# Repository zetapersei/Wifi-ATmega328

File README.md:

# Wifi-ATmega328

A compact embedded board that combines an ESP8266 Wi-Fi module with an ATmega328P microcontroller for projects that need low-cost wireless connectivity and simple MCU control.

## Overview

This project provides a custom PCB designed for applications where an ATmega328P handles the logic and an ESP8266 provides Wi-Fi communication. The design is intended for embedded systems, IoT prototypes, sensor gateways, and small control boards that need a lightweight microcontroller plus wireless connectivity.

The board includes:

- ESP8266 Wi-Fi module
- ATmega328P microcontroller
- power regulation from a 12V / 5V input to the required logic voltages
- ICSP programming interface for the ATmega328P
- KiCad hardware design files for modification and reproduction

## Hardware architecture

The board is built around two processing elements:

- ATmega328P: used for application logic, sensor acquisition, timers, and control tasks
- ESP8266: used for Wi-Fi communication, network connectivity, and possible ESP-Now communication

The supplied power stage converts the board supply into the voltage levels required by the modules. A dedicated ICSP connector allows the ATmega328P to be programmed directly without removing it from the board.

The hardware project is available in the [hardware](./hardware) folder and includes the KiCad schematic and PCB files.

## Software options

The ESP8266 can be used with the AT command firmware, enabling communication with the ATmega328P through serial interfaces. In this setup, the MCU can delegate Wi-Fi tasks to the ESP8266 while continuing to handle local logic.

Recommended software paths:

- [WiFiEspAT library](https://github.com/jandrassy/WiFiEspAT.git) for AT firmware-based Wi-Fi communication
- [WiFiESPNow library](https://github.com/yoursunny/WifiEspNow) for ESP-Now communication scenarios

This makes the board suitable for both classic serial-controlled Wi-Fi use and low-latency peer-to-peer wireless communication.

## Repository structure

- `hardware/` — KiCad project files and PCB design assets
- `README.md` — project overview and documentation
- `LICENSE` — project license information

## Board views

### Top view

### Isometric view

## Typical use cases

- wireless sensor nodes
- smart actuator control boards
- IoT prototypes and test platforms
- embedded projects that need a classic AVR MCU plus Wi-Fi access

This board is especially useful when an AVR-based firmware stack is preferred while still requiring network connectivity through the ESP8266.

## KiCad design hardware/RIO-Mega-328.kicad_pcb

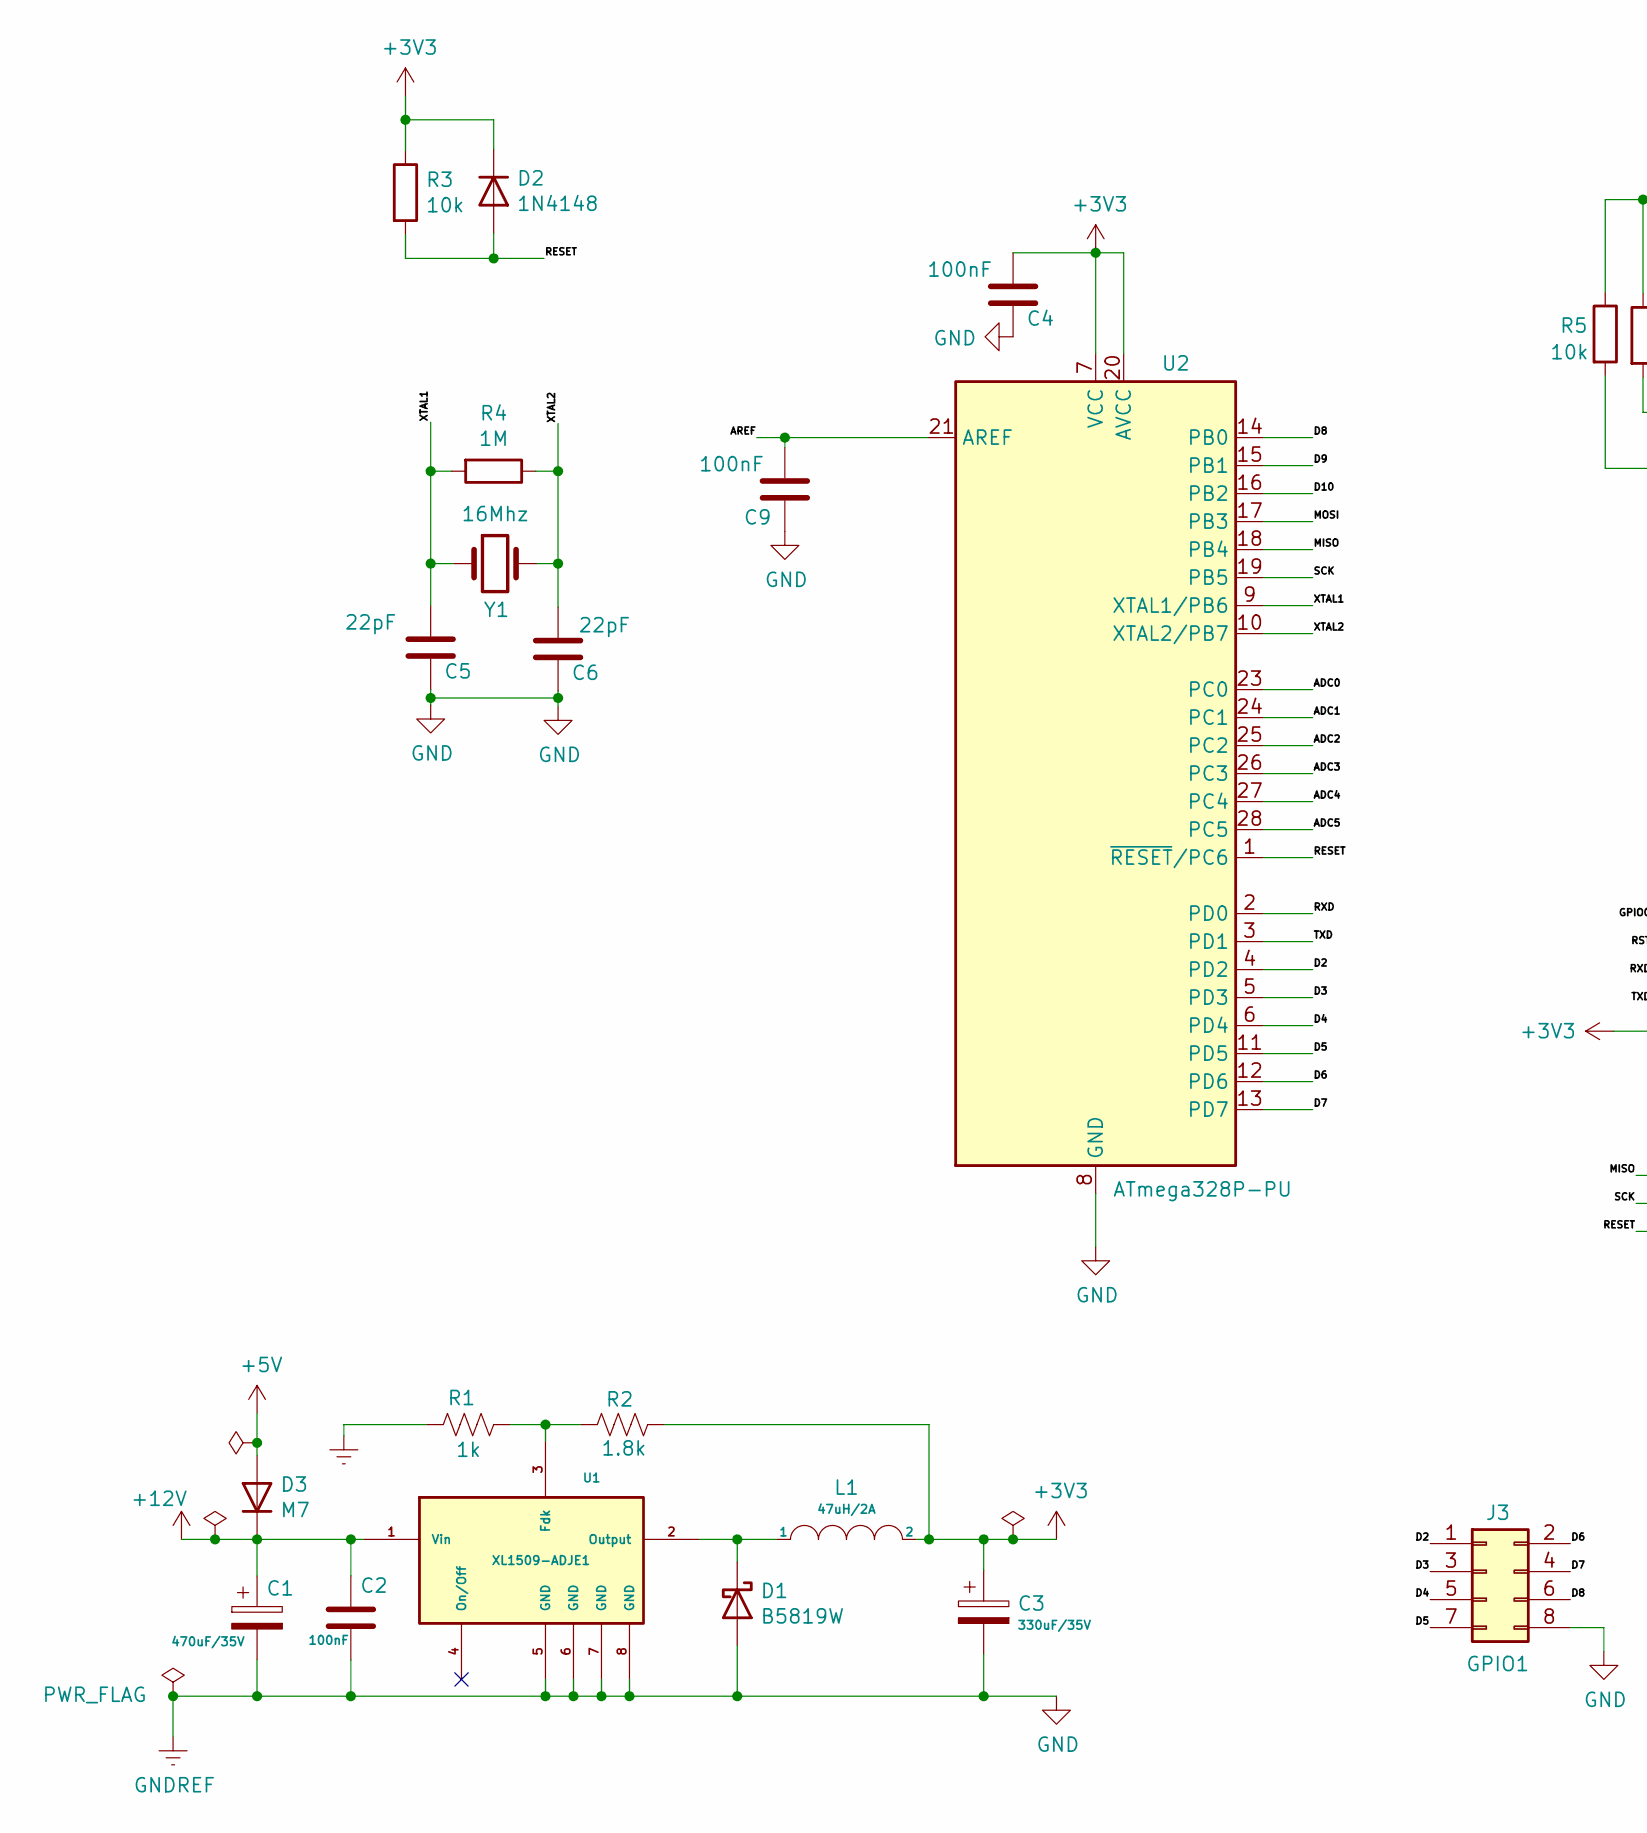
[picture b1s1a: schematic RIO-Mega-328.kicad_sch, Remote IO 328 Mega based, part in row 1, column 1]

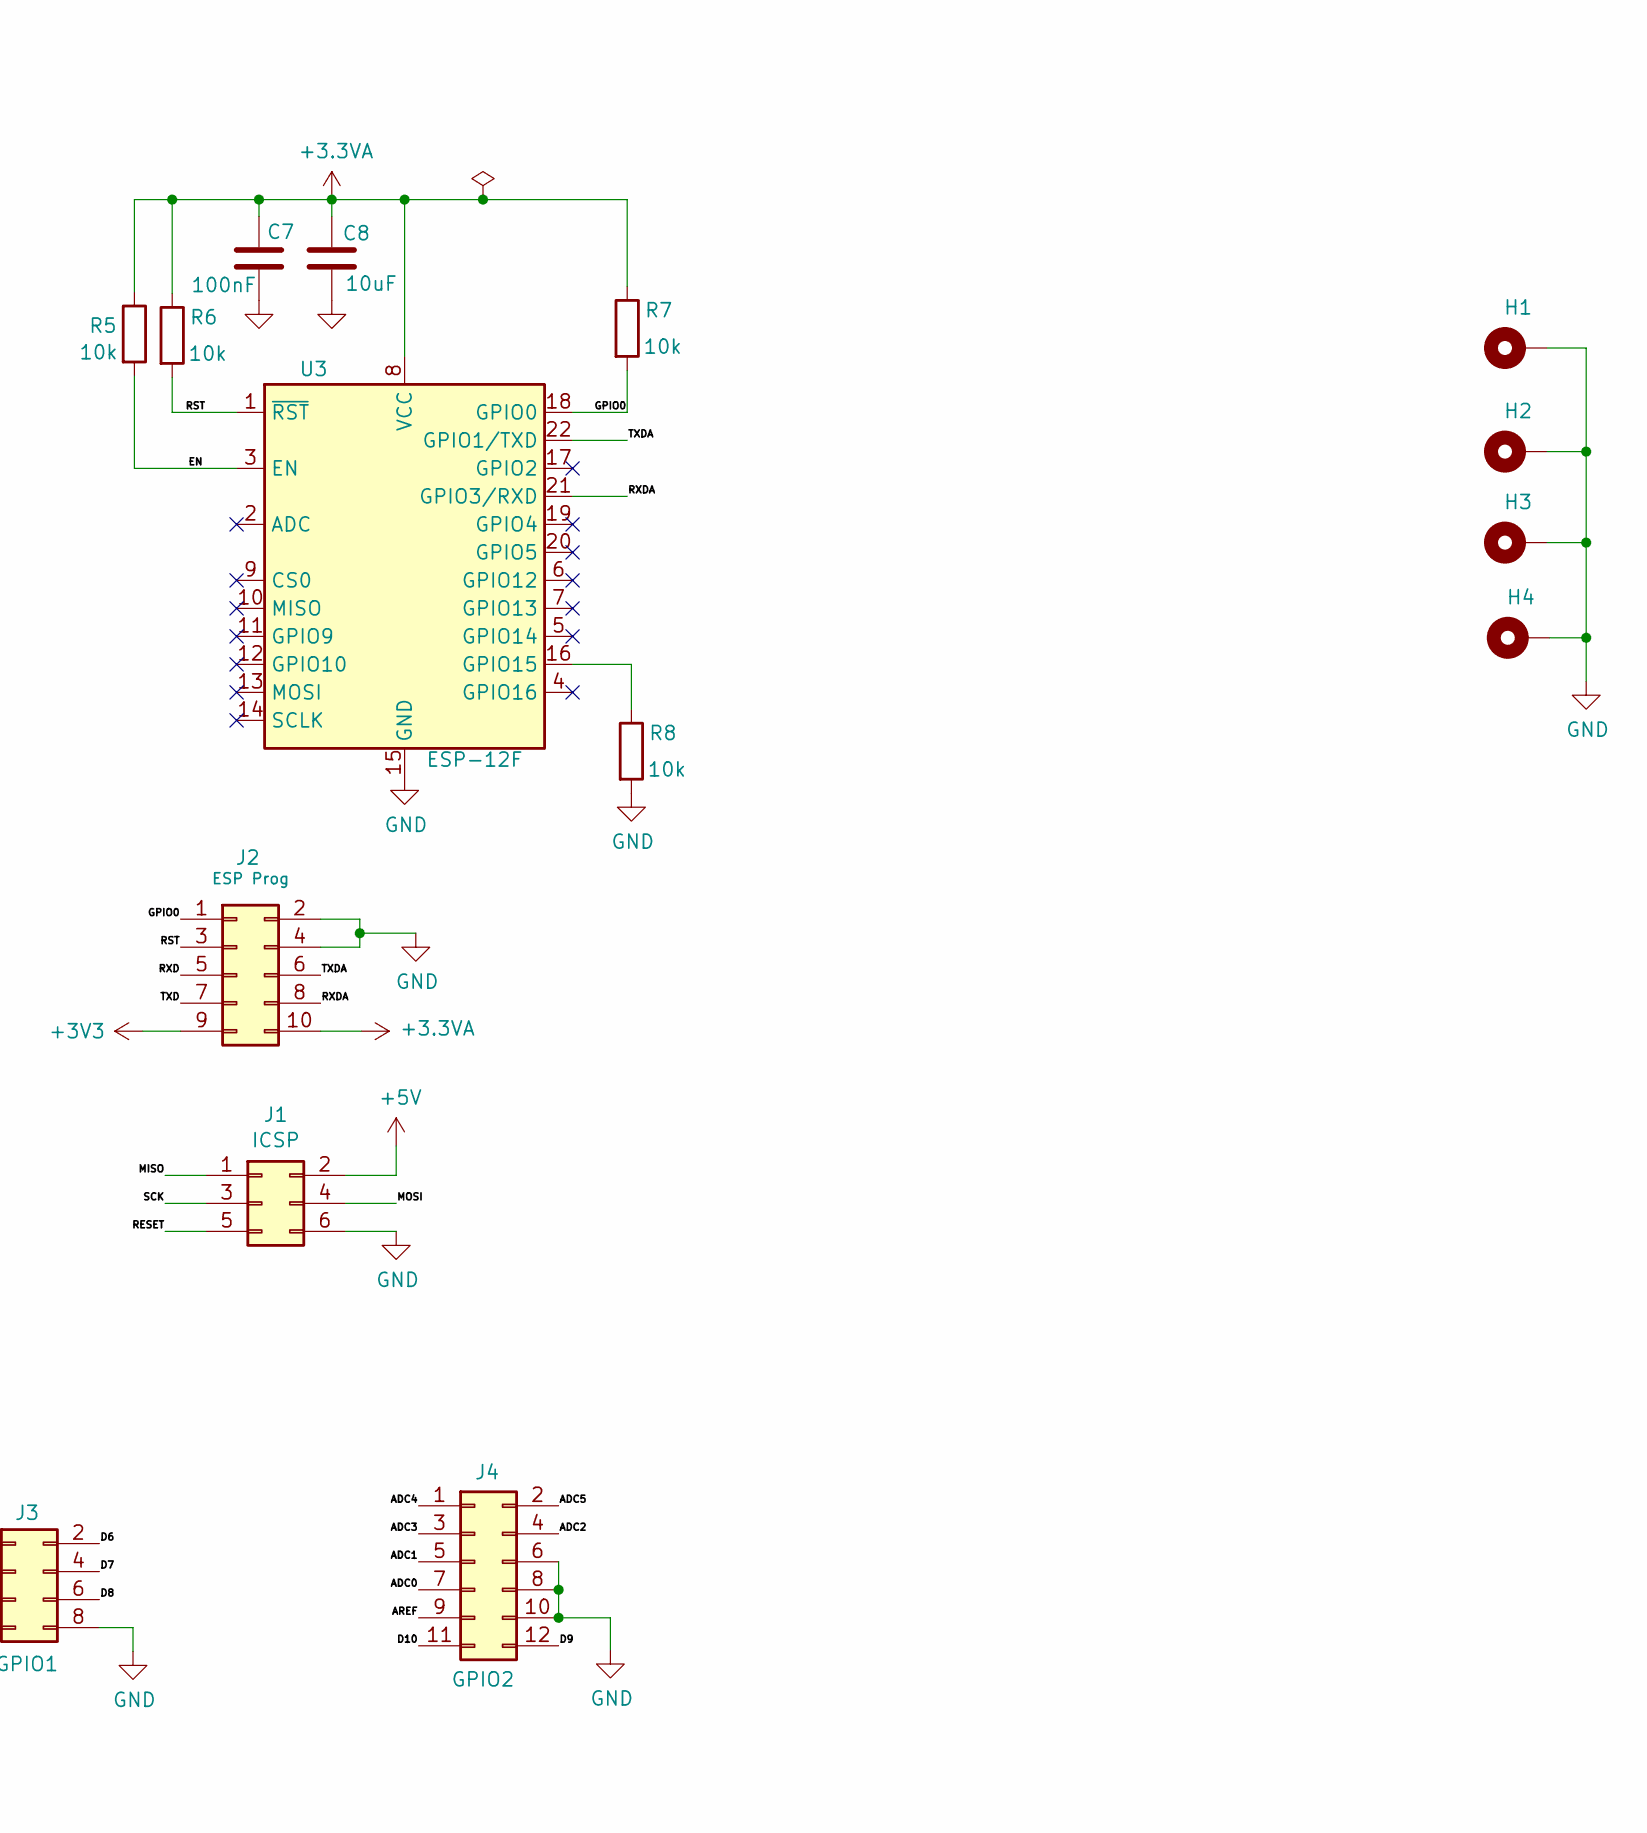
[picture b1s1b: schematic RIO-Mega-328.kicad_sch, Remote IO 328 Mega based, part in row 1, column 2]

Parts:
C1: 470uF/35V; CP_Radial_D8.0mm_P5.00mm
C2, C4, C7, C9: 100nF; C_0402_1005Metric; LCSC C1525
C3: 330uF/35V; CP_Radial_D8.0mm_P5.00mm
C5, C6: 22pF; C_0402_1005Metric; LCSC C1555
C8: 10uF; C_0603_1608Metric; LCSC C19702
D1: B5819W; D_SOD-123F; LCSC C8598
D2: 1N4148; D_SOD-123F; LCSC C81598
D3: M7; D_SOD-128; LCSC C95872
H1, H2, H3, H4: MountingHole_Pad; MountingHole_2.5mm_Pad_Via
J1: ICSP; PinHeader_2x03_P2.54mm_Vertical
J2: ESP Prog; PinHeader_2x05_P2.54mm_Vertical
J3: GPIO1; PinHeader_2x04_P2.54mm_Vertical
J4: GPIO2; PinHeader_2x06_P2.54mm_Vertical
L1: 47uH/2A; L_6.0x6.0x4.5-SWPA-Sunlord; LCSC C36414
R1: 1k; R_0402_1005Metric; LCSC C11702
R2: 1.8k; R_0402_1005Metric; LCSC C4177
R3: 10k; R_0402_1005Metric; LCSC C25774
R4: 1M; R_0603_1608Metric; LCSC C22935
R5, R6, R7, R8: 10k; R_0402_1005Metric; LCSC C25744
U1: XL1509-ADJE1; SOP-8_3.9x4.9mm_P1.27mm; LCSC C74192
U2: ATmega328P-PU; DIP-28_W7.62mm
U3: ESP-12F; ESP-12E; LCSC C82891
Y1: 16Mhz; Crystal_HC18-U_Vertical

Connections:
+3.3VA: C7.1, C8.1, J2.10, R5.1, R6.1, R7.1, U3.8 (VCC)
+3V3: C3.1, C4.1, D2.1 (K), J2.9, L1.2, R2.1, R3.1, U2.7 (VCC), U2.20 (AVCC)
+5V: D3.2 (A), J1.2
+12V: C1.1, C2.1, D3.1 (K), U1.1 (Vin)
/ADC0: J4.7, U2.23 (PC0)
/ADC1: J4.5, U2.24 (PC1)
/ADC2: J4.4, U2.25 (PC2)
/ADC3: J4.3, U2.26 (PC3)
/ADC4: J4.1, U2.27 (PC4)
/ADC5: J4.2, U2.28 (PC5)
/AREF: C9.1, J4.9, U2.21 (AREF)
/D2: J3.1, U2.4 (PD2)
/D3: J3.3, U2.5 (PD3)
/D4: J3.5, U2.6 (PD4)
/D5: J3.7, U2.11 (PD5)
/D6: J3.2, U2.12 (PD6)
/D7: J3.4, U2.13 (PD7)
/D8: J3.6, U2.14 (PB0)
/D9: J4.12, U2.15 (PB1)
/D10: J4.11, U2.16 (PB2)
/EN: R5.2, U3.3 (EN)
/GPIO0: J2.1, R7.2, U3.18 (GPIO0)
/MISO: J1.1, U2.18 (PB4)
/MOSI: J1.4, U2.17 (PB3)
/RESET: D2.2 (A), J1.5, R3.2, U2.1 (~RESET/PC6)
/RST: J2.3, R6.2, U3.1 (~RST)
/RXD: J2.5, U2.2 (PD0)
/RXDA: J2.8, U3.21 (GPIO3/RXD)
/SCK: J1.3, U2.19 (PB5)
/TXD: J2.7, U2.3 (PD1)
/TXDA: J2.6, U3.22 (GPIO1/TXD)
/XTAL1: C5.1, R4.2, U2.9 (XTAL1/PB6), Y1.1
/XTAL2: C6.1, R4.1, U2.10 (XTAL2/PB7), Y1.2
GND: C1.2, C2.2, C3.2, C4.2, C5.2, C6.2, C7.2, C8.2, C9.2, D1.2 (A), H1.1, H2.1, H3.1, H4.1, J1.6, J2.2, J2.4, J3.8, J4.6, J4.8, J4.10, R1.2, R8.2, U1.5 (GND), U1.6 (GND), U1.7 (GND), U1.8 (GND), U2.8 (GND), U2.22 (GND), U3.15 (GND)
unnamed: D1.1 (K), L1.1, U1.2 (Output)
unnamed: R1.1, R2.2, U1.3 (Fdk)
unnamed: R8.1, U3.16 (GPIO15)

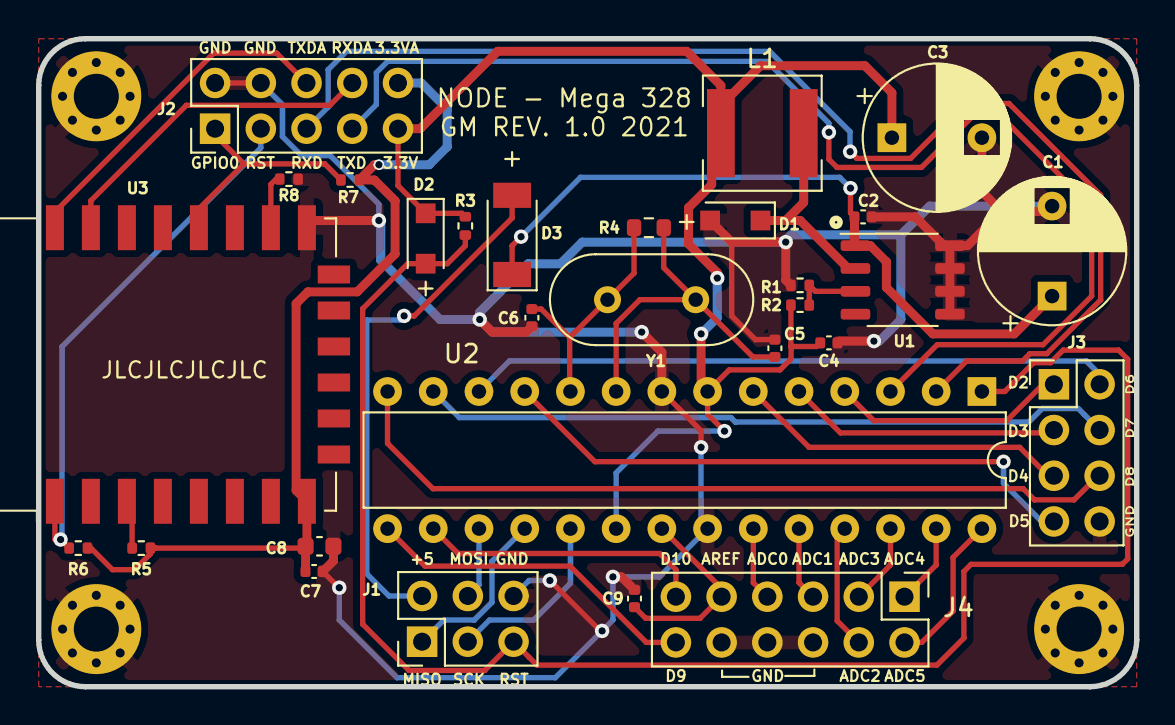
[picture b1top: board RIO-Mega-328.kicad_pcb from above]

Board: 2 copper layers, 61.0 x 36.0 mm, 33 parts (0 on the bottom side), 37 nets.

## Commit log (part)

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2022-11-13 Add library can be used
